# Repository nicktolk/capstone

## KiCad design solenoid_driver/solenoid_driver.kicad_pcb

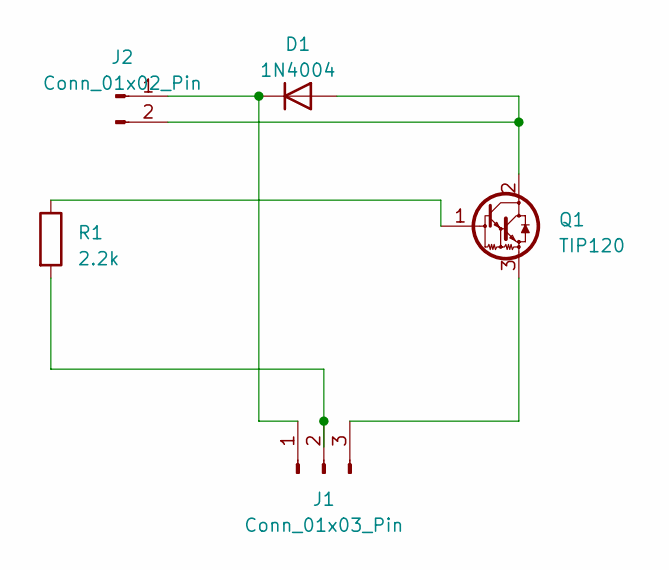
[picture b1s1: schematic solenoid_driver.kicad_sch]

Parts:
D1: 1N4004; D_DO-41_SOD81_P10.16mm_Horizontal
J1: Conn_01x03_Pin; PinHeader_1x03_P2.54mm_Horizontal
J2: Conn_01x02_Pin; PinHeader_1x02_P2.00mm_Vertical
Q1: TIP120; TO-220-3_Vertical
R1: 2.2k; R_Axial_DIN0309_L9.0mm_D3.2mm_P12.70mm_Horizontal

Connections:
unnamed: D1.2 (A), J2.2, Q1.2 (C)
unnamed: D1.1 (K), J1.1, J2.1
unnamed: J1.2, R1.2
unnamed: J1.3, Q1.3 (E)
unnamed: Q1.1 (B), R1.1

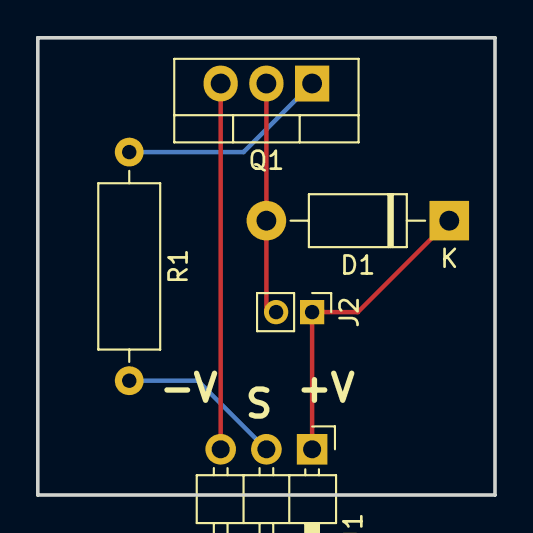
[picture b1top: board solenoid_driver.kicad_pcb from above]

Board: 2 copper layers, 25.4 x 25.4 mm, 5 parts (0 on the bottom side), 5 nets.

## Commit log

2023-04-12 init commit
2023-04-13 added neopixels, mapping, bug fixes
2023-04-14 horizontal detection fix
2023-04-20 field adjustments and cleanup
2023-04-20 removing unused
2023-04-20 removed commented, obsolete code
2023-04-20 cleanup and comments
